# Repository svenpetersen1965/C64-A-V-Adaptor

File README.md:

# C64-A-V-Adaptor
An A/V-adaptor board for the C64
This board is intended to connect to the Commodore C64 and use standard cables (audio, composite with RCA connector and/or s-video with a mini-DIN cable).

It also provides a 330Ohm resistor, which attenuates the s-video chroma line. This resistor can be bridged with a jumper. 

Also an optional stereo output on pin 7 of the a/v jack (stereo sid, FPGA SID etc.) can be connected to the right audio channel. By default, this channel is also connected to the (mono) audio output.

There is another source of the Lumberg DIN connector found for north America: https://www.alliedelec.com/product/lumberg/sv-80/70151558/ 

# Case

I have added a 3D printable case for this adaptor.

# Revision 1
Rev. 1 is exactly the same as Rev. 0, except the spacer, that had to be cut off manually was removed to myke this board a little more mass production friendly. All masures and positions stayed the same. The BOM has not been changed, either (except the PCB Rev. No.).

# Revision 2
In Rev. 2, the obsolete Lumberg BTOR1 RCA jacks are replaced with a model from CUI Inc. Also, there is an alternative from Keystone. Check ou the BOM.

# Prices

I have added a price calculation with prices of May 2020. The  prices per item were retrieved from reichelt.de. They might differ from distributor to distributor (the Lumberg connectors are more expensive in North America) and they don't include any shipping fees.

A standard A/V Adaptor is worth 12,75€ (May 2020) plus the 3D printed case and label.

In September 2022, a new price had to be calculated. The BOM Value is now (Sepüt. 2nd, 2022) 16.63€. 

# VIC-20 & C128

This AV-Adaptor is blocking the Expansion Port of the VIC-20 (the 5 pin version) and the IEC bus of the C128! There are dedicated versions for each.

* <a href="https://github.com/svenpetersen1965/C128-A-V-Adapter">C128 A/V-Adapter</a>
* <a href="https://github.com/svenpetersen1965/VIC-20_AV-Adapter">VIC-20 A/V-Adapter</a>

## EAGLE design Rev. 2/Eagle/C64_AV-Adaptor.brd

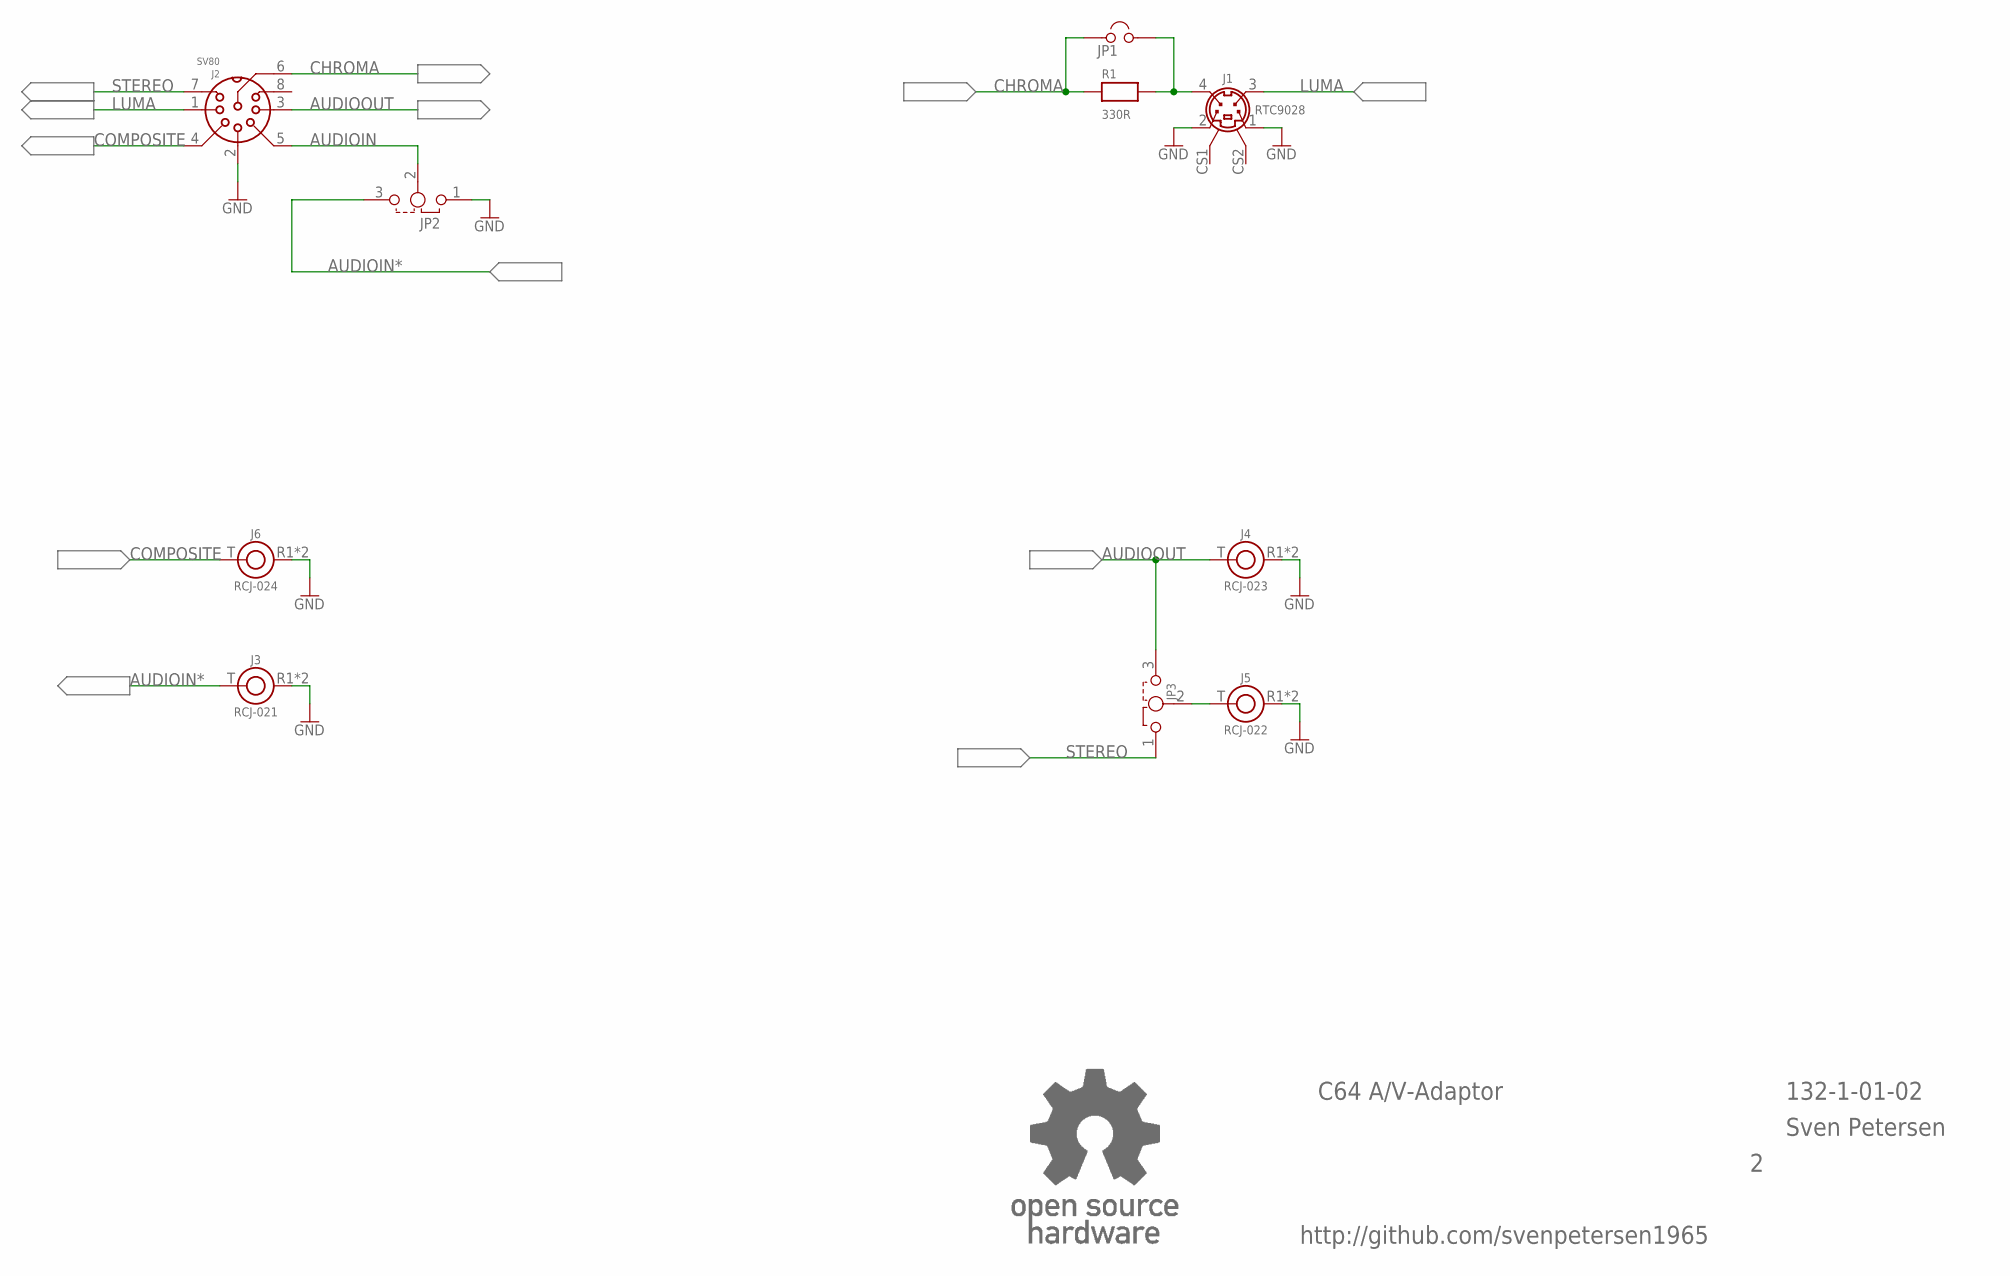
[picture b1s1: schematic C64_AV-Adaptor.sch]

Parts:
J1: RTC9028; MINIDIN4_V
J2: SV80; SV80_INNER
J3: RCJ-021; RCJ-02X
J4: RCJ-023; RCJ-02X
J5: RCJ-022; RCJ-02X
J6: RCJ-024; RCJ-02X
JP1: JUMPER; 1X02
JP2, JP3: DJUMPER; 1X03
R1: 330R; R-10
U$25: OPEN_SOURCE_HW; OPENHW

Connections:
AUDIOIN: J2.5, JP2.2
AUDIOIN*: J3.T, JP2.3
AUDIOOUT: J2.3, J4.T, JP3.3
AUDIOR: J5.T, JP3.2
CHROMA: J2.6, JP1.1, R1.1
COMPOSITE: J2.4, J6.T
GND: J1.1, J1.2, J2.2, J3.R1 (R), J3.R2 (R), J4.R1 (R), J4.R2 (R), J5.R1 (R), J5.R2 (R), J6.R1 (R), J6.R2 (R), JP2.1
LUMA: J1.3, J2.1
unnamed: J1.4, JP1.2, R1.2
STEREO: J2.7, JP3.1

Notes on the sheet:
C64 A/V-Adaptor
132-1-01-02
Sven Petersen
http://github.com/svenpetersen1965

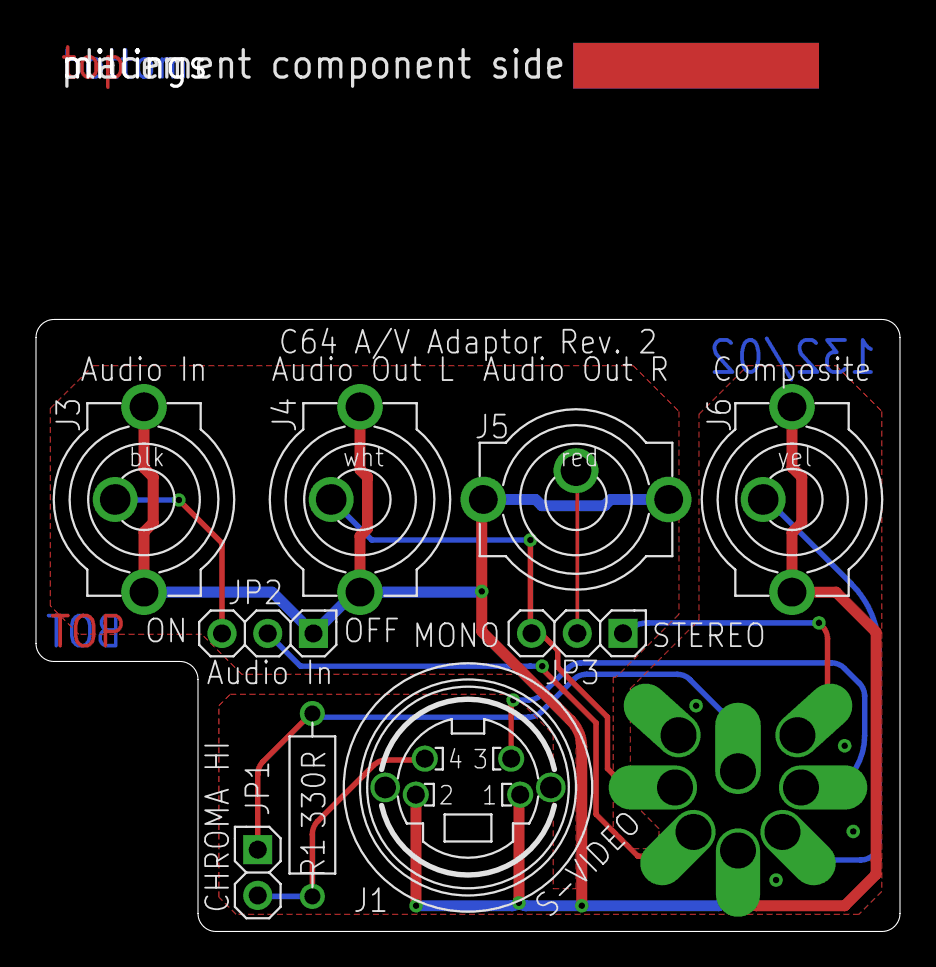
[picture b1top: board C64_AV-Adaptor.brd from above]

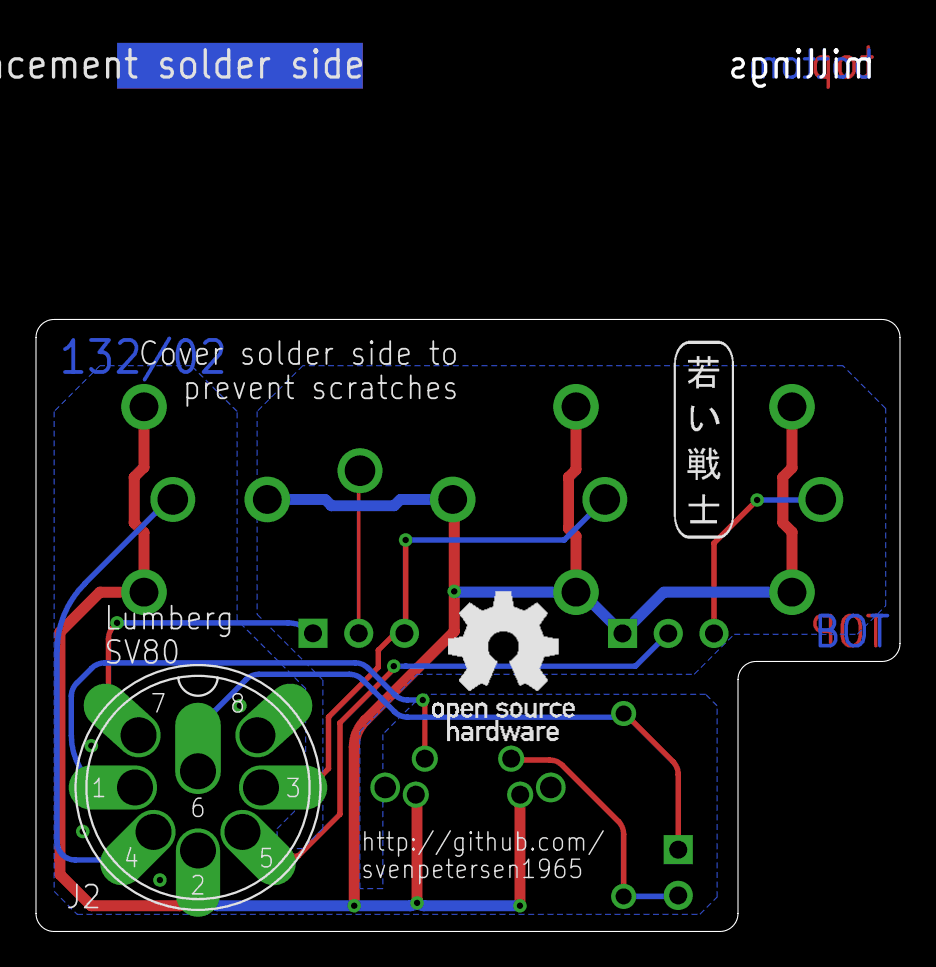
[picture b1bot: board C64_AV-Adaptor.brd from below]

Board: 2 copper layers, 48.0 x 49.7 mm, 14 parts (3 on the bottom side), 10 nets.

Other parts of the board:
U$22: 2LAYER
U$23: SVEN_TAG
U$24: PCB-TITLE/

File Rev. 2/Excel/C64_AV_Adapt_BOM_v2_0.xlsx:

C64 A/V-Adaptor Rev. 2
Bill of Material Rev. 2.0
Pos. | Qty | Value | Footprint | Ref.-No. | Comment
1 | 1 | 132-2-01-02 | 2 Layer | PCB Rev. 2 | 2 layer, Cu 35µ, HASL, 48.0mm x 34.0mm, 1.6mm FR4
2 | 2 | 1x 3p pin header, pitch 2.54mm | 1X03 | JP2, JP3 | standard pin header, e.g. Reichelt RND 205-00624, not required for 5-pin and VI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
3 | 1 | 1x 2p pin header, pitch 2.54mm | 1X02 | JP1 | standard pin header, e.g. Reichelt RND 205-00623, not required for 5-pin and VI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
4 | 3 | Jumper 2.54mm pitch | jumper | (JP1), (JP2), (JP3) | Jumper (0,1") with holder/latch, e.g. tme.eu: JUMPER-H/B, Farnell: 2396301, New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
5 | 1 | 330R | R-10 | R1 | resistor, 0.25W or more, 5% or better. Not required for 5-pin and VIC-20
6 | 1 | RCJ-022 | RCJ-02X | J5 | CUI Inc., RCA jack, vertical, red. Mouser: 490-RCJ-022, Digikey: CP-1407-ND. Al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
7 | 1 | RCJ-023 | RCJ-02X | J4 | CUI Inc., RCA jack, vertical, white. Mouser: 490-RCJ-023, Digikey: CP-1408-ND. 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
8 | 1 | RCJ-021 | RCJ-02X | J3 | CUI Inc., RCA jack, vertical, black. Mouser: 490-RCJ-021, Digikey: CP-1406-ND. 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
9 | 1 | RCJ-024 | RCJ-02X | J6 | CUI Inc., RCA jack, vertical, yellow. Mouser: 490-RCJ-024, Digikey: CP-1409-ND.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
10 | 1 | RTC9028 | MINIDIN4_V | J1 | Mini-DIN, 4p, vertical. Not required for 5-pin. E.g. AliExpress:
 |  |  |  |  | RTConnector: RTC9028
 |  |  |  |  | ebay.de
11 | 1 | SV80 | SV80_INNER | J2 | Inner part of Lumberg 033099 SV 80, e.G. Reichelt: LUM SV 80, Newark: 23AH4043,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
 |  | Rev. History
 |  | v0.0 ® v0.1
Pos 4 |  | now with latch
 |  | three models
 |  | v0.1 ® v.1.0
Pos 1 |  | PCB revision (no spacer)
 |  | v1.0 ® v.2.0
Pos 1 |  | PCB Revision
Pos 6 |  | replaced obsolete part
Pos 7 |  | replaced obsolete part
Pos 8 |  | replaced obsolete part
Pos 9 |  | replaced obsolete part

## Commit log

2019-10-12 Initial upload
2019-10-12 Add files via upload
    Library, which contains the footprint of the Lumberg SV 80 insert.
2019-10-21 BOM v0.1 added
    Added a new version of the BOM with jumpers with a latch. This is an improvement in case the 3D printed case is used.
2019-11-09 Versions for ASSY326298 C64 and VIC-20
    New versions, the original C64 8-pin was slightly modified (no bevelling around the RCA jacks for better decals.
2019-11-09 Decals for all versions added
2019-11-09 Delete top shell.stl
    other naming
2019-11-09 top shell for regular, ASSY326298 and VIC-20
    New versions added
2019-11-09 inkscape files for the decals
2019-11-13 Three models documentation
2020-01-02 Rev. 1 released
2020-01-02 Revision History added
2020-05-26 Added a price calculation
2020-08-10 Silk Screen Update
2021-06-03 Label as PNG
2022-02-26 Gerbers removed
2022-09-02 Case for PCB Rev. 2
2022-09-02 PCB Rev. 2 released
2022-09-14 version without header
    Some pcb manufacturer don't get along with my 25 year old header.
2022-09-14 gerber version without
    For picky pcb manufacturers.
2022-11-08 Add files via upload
    Nice label added (with colored Commodore logo)
